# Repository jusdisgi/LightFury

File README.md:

# Light Fury

This is a 54-key, ergonomic split keyboard with a few tricks. Some of the features include:
- 1.69in color [LCD screen](https://www.waveshare.com/product/displays/lcd-oled/lcd-oled-3/1.69inch-lcd-module.htm)
- Per-key LEDs, using [WS2812B-2020](https://www.adafruit.com/product/4684)
- A roller encoder based on [CKW12](https://github.com/kumamuk-git/CKW12/tree/main) by Kumamuk, but integrated into the main PCB
- Kailh [PG1316S](https://holykeebs.com/products/kailh-pg1316s-butterfly-switch-10-pack) ultra-low profile switches
- A totally absurd [battery](https://www.digikey.com/en/products/detail/maker-emporium-ltd/PIS-1131/13283430) to run all of this stuff...5Ahr!!

## Schematics and Ergogen, just like PB and Chocolate!
If that seems absurd to you, you need to read [my new doc](https://github.com/jusdisgi/LightFury/blob/main/Schematics_and_Ergogen.md)

## Work in Progress

I think it might be done? Could it be?
Please take a look and let me know if you see anything wrong!

## Where is everything?
[Left Half PCB](https://github.com/jusdisgi/LightFury/blob/main/lightfury_left.kicad_pcb)
[Right Half PCB](https://github.com/jusdisgi/LightFury/blob/main/lightfury_right.kicad_pcb)

[Left Half Schematic](https://github.com/jusdisgi/LightFury/blob/main/lightfury_left.kicad_sch)
[Right Half Schematic](https://github.com/jusdisgi/LightFury/blob/main/lightfury_right.kicad_sch)

[Ergogen Config](https://github.com/jusdisgi/LightFury/blob/main/config.yaml)

## Some pics of the design

*the name has been chosen by the intended end-user, but will not be applied to the board until it actually exists in the real world.

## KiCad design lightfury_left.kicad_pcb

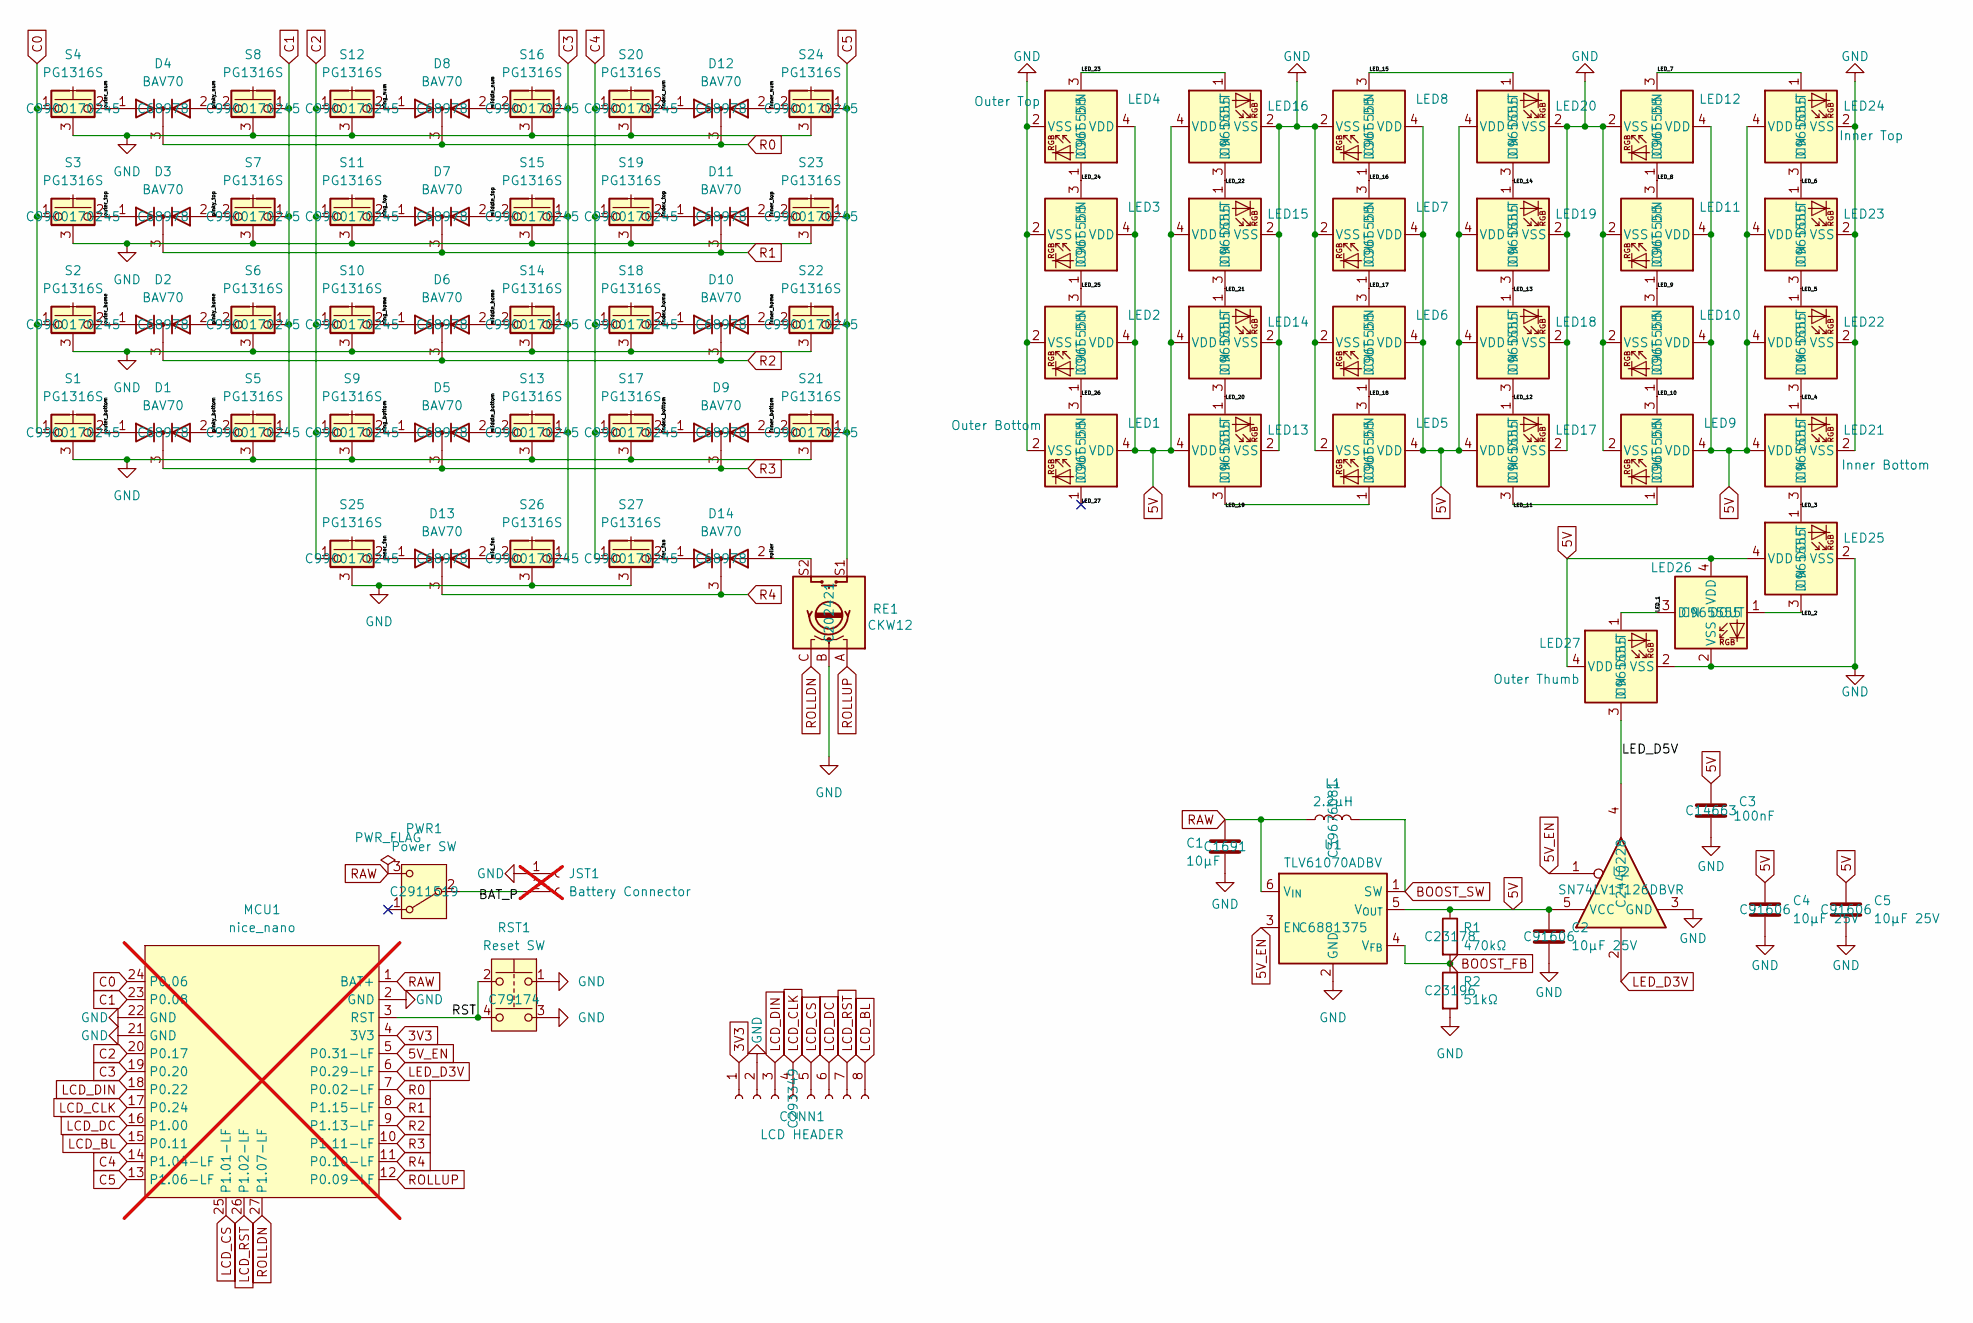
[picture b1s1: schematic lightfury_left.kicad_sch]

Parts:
C1: 10μF; C_0603_1608Metric; LCSC C1691
C2: 10μF 25V; C_0603_1608Metric; LCSC C91606
C3: 100nF; C_0603_1608Metric; LCSC C14663
C4, C5: 10µF 25V; C_0603_1608Metric; LCSC C91606
CONN1: LCD HEADER; Molex_PicoBlade_53261-0871_1x08-1MP_P1.25mm_Horizontal; LCSC C293349
D1, D2, D3, D4, D5, D6, D7, D8, D9, D10, D11, D12, D13, D14: BAV70; BAV70 SOT23; LCSC C68978
JST1: Battery Connector; battery_connector_jst_ph_2; not fitted
L1: 2.2μH; L_CJIANG_FTC404030S_4.1x4.1x3.0_SMD; LCSC C39676081
LED1: Outer Bottom; LED_WS2812B-2020_PLCC4_2.0x2.0mm; LCSC C965555
LED2, LED3, LED5, LED6, LED7, LED8, LED9, LED10, LED11, LED12, LED13, LED14, LED15, LED16, LED17, LED18, LED19, LED20, LED22, LED23, LED25, LED26: WS2812B-2020; LED_WS2812B-2020_PLCC4_2.0x2.0mm; LCSC C965555
LED4: Outer Top; LED_WS2812B-2020_PLCC4_2.0x2.0mm; LCSC C965555
LED21: Inner Bottom; LED_WS2812B-2020_PLCC4_2.0x2.0mm; LCSC C965555
LED24: Inner Top; LED_WS2812B-2020_PLCC4_2.0x2.0mm; LCSC C965555
LED27: Outer Thumb; LED_WS2812B-2020_PLCC4_2.0x2.0mm; LCSC C965555
MCU1: nice_nano; mcu_nice_nano; not fitted
PWR1: Power SW; power_switch_smd_side; LCSC C2911519
R1: 470kΩ; R_0603_1608Metric; LCSC C23178
R2: 51kΩ; R_0603_1608Metric; LCSC C23196
RE1: CKW12; LCSC C202421
RST1: Reset SW; reset_switch_smd_side; LCSC C79174
S1, S2, S3, S4, S5, S6, S7, S8, S9, S10, S11, S12, S13, S14, S15, S16, S17, S18, S19, S20, S21, S22, S23, S24, S25, S26, S27: PG1316S; LCSC C9900170245
U1: TLV61070ADBV; SOT-23-6; LCSC C6881375
U2: SN74LV1T126DBVR; SOT-23-5; LCSC C2440228

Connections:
3V3: CONN1.1, MCU1.4 (3V3)
5V: C2.1, C3.1, C4.1, C5.1, LED1.4 (VDD), LED2.4 (VDD), LED3.4 (VDD), LED4.4 (VDD), LED5.4 (VDD), LED6.4 (VDD), LED7.4 (VDD), LED8.4 (VDD), LED9.4 (VDD), LED10.4 (VDD), LED11.4 (VDD), LED12.4 (VDD), LED13.4 (VDD), LED14.4 (VDD), LED15.4 (VDD), LED16.4 (VDD), LED17.4 (VDD), LED18.4 (VDD), LED19.4 (VDD), LED20.4 (VDD), LED21.4 (VDD), LED22.4 (VDD), LED23.4 (VDD), LED24.4 (VDD), LED25.4 (VDD), LED26.4 (VDD), LED27.4 (VDD), R1.1, U1.5 (V_{OUT}), U2.5 (VCC)
5V_EN: MCU1.5 (P0.31-LF), U1.3 (EN), U2.1
/BAT_P: JST1.2, PWR1.2 (B)
/LED_1: LED26.3 (DIN), LED27.1 (DOUT)
/LED_2: LED25.3 (DIN), LED26.1 (DOUT)
/LED_3: LED21.3 (DIN), LED25.1 (DOUT)
/LED_4: LED21.1 (DOUT), LED22.3 (DIN)
/LED_5: LED22.1 (DOUT), LED23.3 (DIN)
/LED_6: LED23.1 (DOUT), LED24.3 (DIN)
/LED_7: LED12.3 (DIN), LED24.1 (DOUT)
/LED_8: LED11.3 (DIN), LED12.1 (DOUT)
/LED_9: LED10.3 (DIN), LED11.1 (DOUT)
/LED_10: LED9.3 (DIN), LED10.1 (DOUT)
/LED_11: LED9.1 (DOUT), LED17.3 (DIN)
/LED_12: LED17.1 (DOUT), LED18.3 (DIN)
/LED_13: LED18.1 (DOUT), LED19.3 (DIN)
/LED_14: LED19.1 (DOUT), LED20.3 (DIN)
/LED_15: LED8.3 (DIN), LED20.1 (DOUT)
/LED_16: LED7.3 (DIN), LED8.1 (DOUT)
/LED_17: LED6.3 (DIN), LED7.1 (DOUT)
/LED_18: LED5.3 (DIN), LED6.1 (DOUT)
/LED_19: LED5.1 (DOUT), LED13.3 (DIN)
/LED_20: LED13.1 (DOUT), LED14.3 (DIN)
/LED_21: LED14.1 (DOUT), LED15.3 (DIN)
/LED_22: LED15.1 (DOUT), LED16.3 (DIN)
/LED_23: LED4.3 (DIN), LED16.1 (DOUT)
/LED_24: LED3.3 (DIN), LED4.1 (DOUT)
/LED_25: LED2.3 (DIN), LED3.1 (DOUT)
/LED_26: LED1.3 (DIN), LED2.1 (DOUT)
/LED_27: LED1.1 (DOUT)
/LED_D5V: LED27.3 (DIN), U2.4
/RST: MCU1.3 (RST), RST1.2, RST1.4
/far_fan: D14.1 (A), S27.2
/index_bottom: D9.1 (A), S17.2
/index_home: D10.1 (A), S18.2
/index_num: D12.1 (A), S20.2
/index_top: D11.1 (A), S19.2
/inner_bottom: D9.2 (A), S21.2
/inner_home: D10.2 (A), S22.2
/inner_num: D12.2 (A), S24.2
/inner_top: D11.2 (A), S23.2
/mid_fan: D13.2 (A), S26.2
/middle_bottom: D5.2 (A), S13.2
/middle_home: D6.2 (A), S14.2
/middle_num: D8.2 (A), S16.2
/middle_top: D7.2 (A), S15.2
/near_fan: D13.1 (A), S25.2
/outer_bottom: D1.1 (A), S1.2
/outer_home: D2.1 (A), S2.2
/outer_num: D4.1 (A), S4.2
/outer_top: D3.1 (A), S3.2
/pinky_bottom: D1.2 (A), S5.2
/pinky_home: D2.2 (A), S6.2
/pinky_num: D4.2 (A), S8.2
/pinky_top: D3.2 (A), S7.2
/ring_bottom: D5.1 (A), S9.2
/ring_home: D6.1 (A), S10.2
/ring_num: D8.1 (A), S12.2
/ring_top: D7.1 (A), S11.2
/roller: D14.2 (A), RE1.S2
BOOST_FB: R1.2, R2.1, U1.4 (V_{FB})
BOOST_SW: L1.2, U1.1 (SW)
C0: MCU1.24 (P0.06), S1.1, S2.1, S3.1, S4.1
C1: MCU1.23 (P0.08), S5.1, S6.1, S7.1, S8.1
C2: MCU1.20 (P0.17), S9.1, S10.1, S11.1, S12.1, S25.1
C3: MCU1.19 (P0.20), S13.1, S14.1, S15.1, S16.1, S26.1
C4: MCU1.14 (P1.04-LF), S17.1, S18.1, S19.1, S20.1, S27.1
C5: MCU1.13 (P1.06-LF), RE1.S1, S21.1, S22.1, S23.1, S24.1
GND: C1.2, C2.2, C3.2, C4.2, C5.2, CONN1.2, JST1.1, LED1.2 (VSS), LED2.2 (VSS), LED3.2 (VSS), LED4.2 (VSS), LED5.2 (VSS), LED6.2 (VSS), LED7.2 (VSS), LED8.2 (VSS), LED9.2 (VSS), LED10.2 (VSS), LED11.2 (VSS), LED12.2 (VSS), LED13.2 (VSS), LED14.2 (VSS), LED15.2 (VSS), LED16.2 (VSS), LED17.2 (VSS), LED18.2 (VSS), LED19.2 (VSS), LED20.2 (VSS), LED21.2 (VSS), LED22.2 (VSS), LED23.2 (VSS), LED24.2 (VSS), LED25.2 (VSS), LED26.2 (VSS), LED27.2 (VSS), MCU1.2 (GND), MCU1.21 (GND), MCU1.22 (GND), R2.2, RE1.B, RST1.1, RST1.3, S1.3 (B), S2.3 (B), S3.3 (B), S4.3 (B), S5.3 (B), S6.3 (B), S7.3 (B), S8.3 (B), S9.3 (B), S10.3 (B), S11.3 (B), S12.3 (B), S13.3 (B), S14.3 (B), S15.3 (B), S16.3 (B), S17.3 (B), S18.3 (B), S19.3 (B), S20.3 (B), S21.3 (B), S22.3 (B), S23.3 (B), S24.3 (B), S25.3 (B), S26.3 (B), S27.3 (B), U1.2 (GND), U2.3 (GND)
LCD_BL: CONN1.8, MCU1.15 (P0.11)
LCD_CLK: CONN1.4, MCU1.17 (P0.24)
LCD_CS: CONN1.5, MCU1.25 (P1.01-LF)
LCD_DC: CONN1.6, MCU1.16 (P1.00)
LCD_DIN: CONN1.3, MCU1.18 (P0.22)
LCD_RST: CONN1.7, MCU1.26 (P1.02-LF)
LED_D3V: MCU1.6 (P0.29-LF), U2.2
R0: D4.3 (K), D8.3 (K), D12.3 (K), MCU1.7 (P0.02-LF)
R1: D3.3 (K), D7.3 (K), D11.3 (K), MCU1.8 (P1.15-LF)
R2: D2.3 (K), D6.3 (K), D10.3 (K), MCU1.9 (P1.13-LF)
R3: D1.3 (K), D5.3 (K), D9.3 (K), MCU1.10 (P1.11-LF)
R4: D13.3 (K), D14.3 (K), MCU1.11 (P0.10-LF)
RAW: C1.1, L1.1, MCU1.1 (BAT+), PWR1.3 (C), U1.6 (V_{IN})
ROLLDN: MCU1.27 (P1.07-LF), RE1.C
ROLLUP: MCU1.12 (P0.09-LF), RE1.A

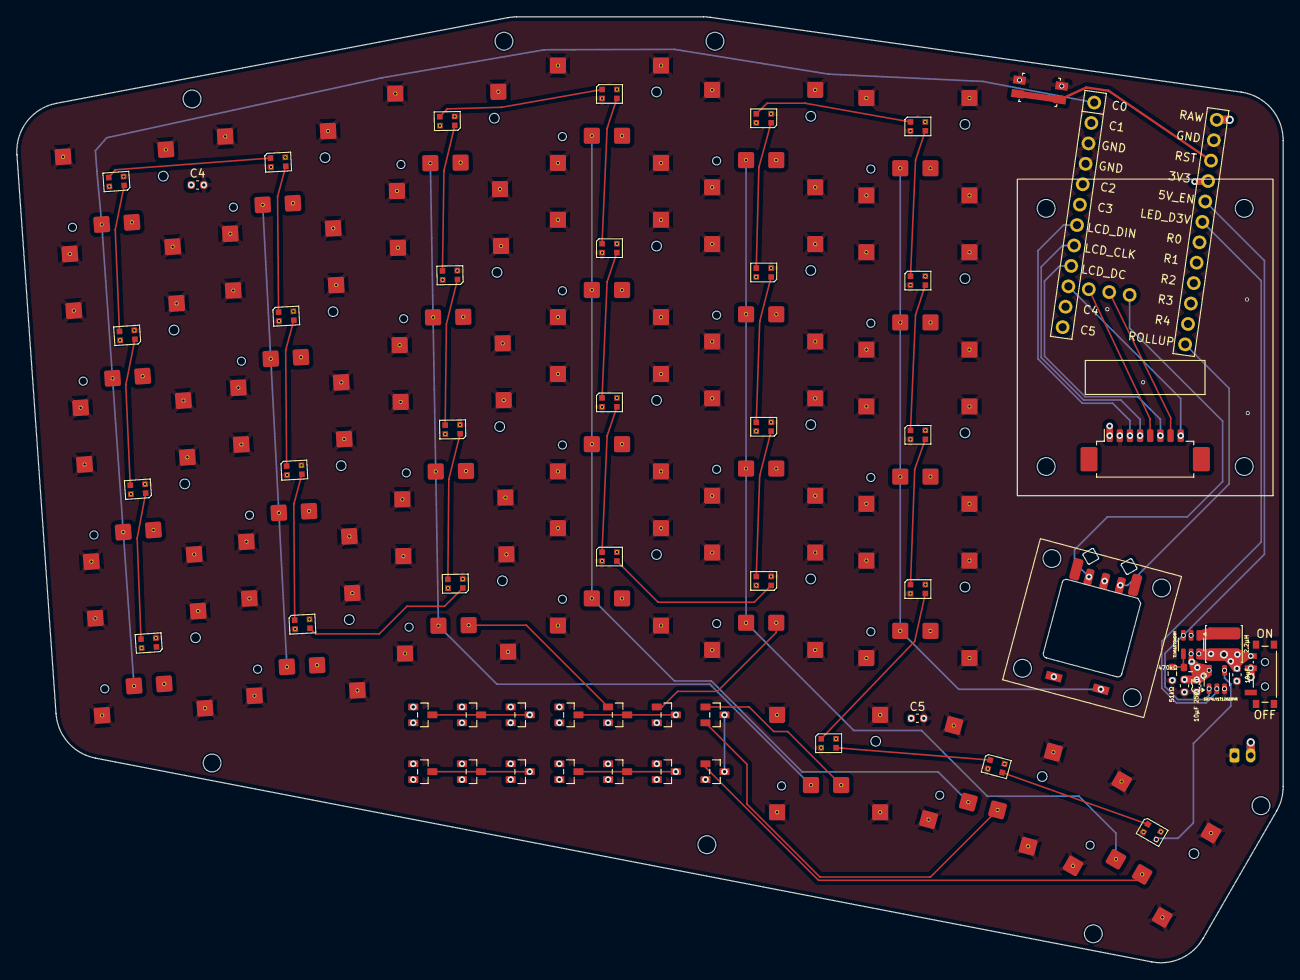
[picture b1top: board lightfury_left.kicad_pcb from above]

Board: 6 copper layers, 156.0 x 116.5 mm, 92 parts (1 on the bottom side), 84 nets.

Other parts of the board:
LCD1: LCD_1.69_Waveshare
MH1, MH2, MH3, MH4, MH5, MH6, MH7: mounting_hole_npth

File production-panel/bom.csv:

Designator,Footprint,Quantity,Value,LCSC Part #
"D1, D10, D10_2, D11, D11_2, D12, D12_2, D13, D13_2, D14, D14_2, D1_2, D2, D2_2, D3, D3_2, D4, D4_2, D5, D5_2, D6, D6_2, D7, D7_2, D8, D8_2, D9, D9_2",BAV70 SOT23,28,BAV70,C68978
"S1, S10, S10_2, S11, S11_2, S12, S12_2, S13, S13_2, S14, S14_2, S15, S15_2, S16, S16_2, S17, S17_2, S18, S18_2, S19, S19_2, S1_2, S2, S20, S20_2, S21, S21_2, S22, S22_2, S23, S23_2, S24, S24_2, S25, S25_2, S26, S26_2, S27, S27_2, S2_2, S3, S3_2, S4, S4_2, S5, S5_2, S6, S6_2, S7, S7_2, S8, S8_2, S9, S9_2",PG1316S,54,PG1316S,C9900170245
"R2, R2_2",Resistor_SMD:R_0603_1608Metric,2,51kΩ,C23196
"RE1, RE1_2",CKW12,2,CKW12,C202421
"LED1, LED10, LED10_2, LED11, LED11_2, LED12, LED12_2, LED13, LED13_2, LED14, LED14_2, LED15, LED15_2, LED16, LED16_2, LED17, LED17_2, LED18, LED18_2, LED19, LED19_2, LED1_2, LED2, LED20, LED20_2, LED21, LED21_2, LED22, LED22_2, LED23, LED23_2, LED24, LED24_2, LED25, LED25_2, LED26, LED26_2, LED27, LED27_2, LED2_2, LED3, LED3_2, LED4, LED4_2, LED5, LED5_2, LED6, LED6_2, LED7, LED7_2, LED8, LED8_2, LED9, LED9_2",LED_WS2812B-2020_PLCC4_2.0x2.0mm,54,WS2812B-2020,C965555
"R1, R1_2",Resistor_SMD:R_0603_1608Metric,2,470kΩ,C23178
"RST1, RST1_2",ceoloide:reset_switch_smd_side,2,Reset SW,C79174
"CONN1, CONN1_2",Molex_PicoBlade_53261-0871_1x08-1MP_P1.25mm_Horizontal,2,LCD HEADER,C293349
"C2, C2_2, C4, C4_2, C5, C5_2",Capacitor_SMD:C_0603_1608Metric,6,10μF 25V,C91606
"C3, C3_2",Capacitor_SMD:C_0603_1608Metric,2,100nF,C14663
"U2, U2_2",Package_TO_SOT_SMD:SOT-23-5,2,SN74LV1T126DBVR,C2440228
"PWR1, PWR1_2",ceoloide:power_switch_smd_side,2,Power SW,C2911519
"L1, L1_2",huntercook:L_CJIANG_FTC404030S_4.1x4.1x3.0_SMD,2,2.2μH,C39676081
"U1, U1_2",Package_TO_SOT_SMD:SOT-23-6,2,TLV61070ADBV,C6881375
"C1, C1_2",Capacitor_SMD:C_0603_1608Metric,2,10μF,C1691
"RESW1, RESW1_2",CKW12,2,CKW12 Switch,C262417

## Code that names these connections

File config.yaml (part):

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    bav70_bottom1: &bav70proto #Ref: D1
      key:
        A1: outer_bottom
        A2: pinky_bottom
        C: R3
      anchor: &bav70anchor
        - ref: finger_middle_bottom
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    bav70_home1: #Ref: D2
      <<:  *bav70proto
      key.A1: outer_home
      key.A2: pinky_home
      key.C: R2
      anchor:
        <<: *bav70anchor
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    bav70_top1: #Ref: D3
      <<:  *bav70proto
      key.A1: outer_top
      key.A2: pinky_top
      key.C: R1
      anchor:
        <<: *bav70anchor
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    bav70_num1: #Ref: D4
      <<:  *bav70proto
      key.A1: outer_num
      key.A2: pinky_num
      key.C: R0
      anchor:
        <<: *bav70anchor
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
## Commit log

2025-06-18 Add all the stuff.
2026-06-04 Prep for review and paneling
2026-06-04 Added capacitors for 5v load smoothing.
2026-06-05 more clean
2026-06-18 Add LCSC field and populate for BOM.
2026-06-18 Panelize board, generate production files. Production candidate.
2026-06-26 Cleanup
2026-06-26 Add new production files.
